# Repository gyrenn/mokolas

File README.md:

# mokolas
mokolo mokolok mokoloja

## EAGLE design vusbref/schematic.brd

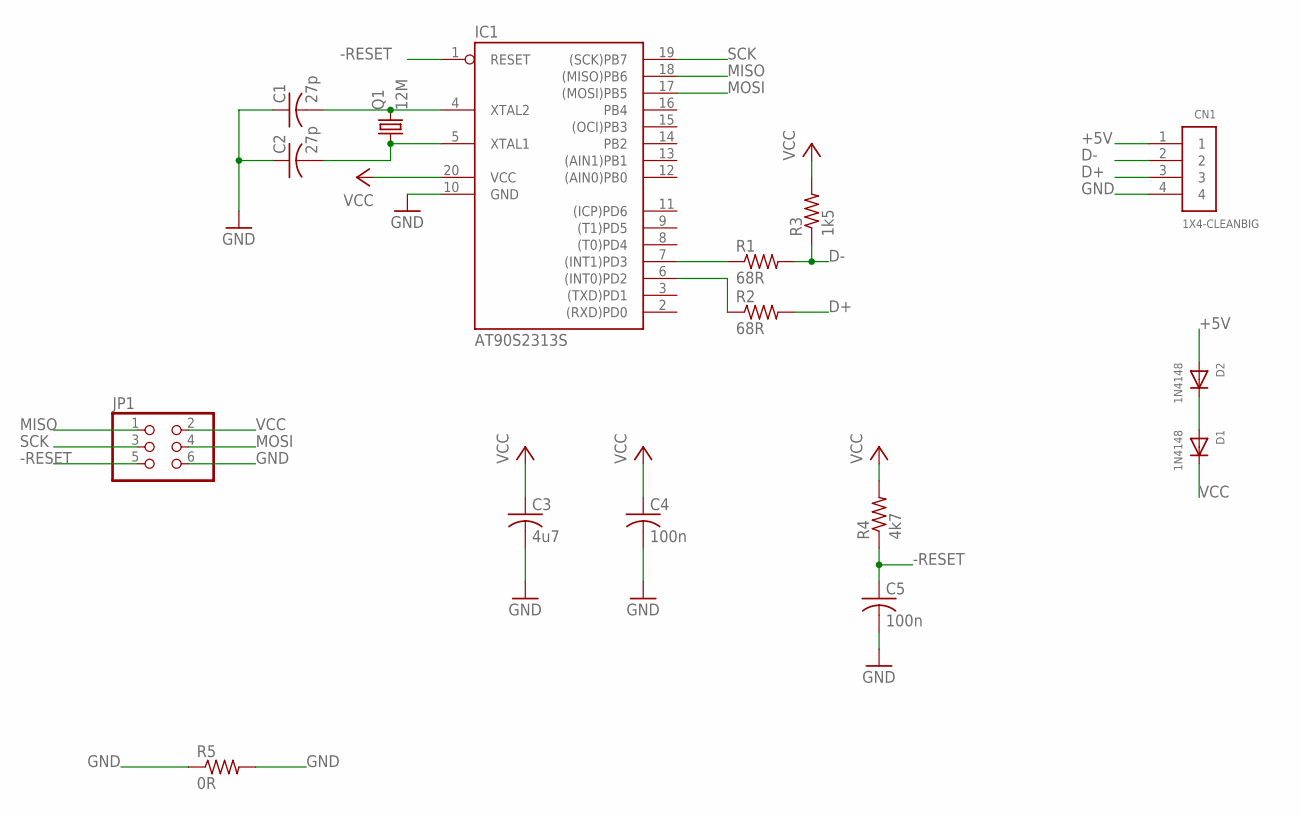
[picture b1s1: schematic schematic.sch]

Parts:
C1, C2: 27p; C0805
C3: 4u7; C0805
C4, C5: 100n; C0805
CN1: 1X4-CLEANBIG; 1X04-CLEANBIG
D1, D2: 1N4148; SMADIODE
IC1: AT90S2313S; SO20L
JP1: PINHD-2X3; 2X03
Q1: 12M; HC49UP
R1, R2: 68R; R0805
R3: 1k5; R0805
R4: 4k7; R0805
R5: 0R; R1206

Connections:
+5V: CN1.1, D2.A
-RESET: C5.1, IC1.1 (RESET), JP1.5, R4.1
D+: CN1.3, R2.2
D-: CN1.2, R1.2, R3.1
GND: C1.1, C2.1, C3.2, C4.2, C5.2, CN1.4, IC1.10 (GND), JP1.6, R5.1, R5.2
MISO: IC1.18 ((MISO)PB6), JP1.1
MOSI: IC1.17 ((MOSI)PB5), JP1.4
unnamed: C1.2, IC1.4 (XTAL2), Q1.2
unnamed: C2.2, IC1.5 (XTAL1), Q1.1
unnamed: IC1.7 ((INT1)PD3), R1.1
unnamed: D1.A, D2.C
unnamed: IC1.6 ((INT0)PD2), R2.1
SCK: IC1.19 ((SCK)PB7), JP1.3
VCC: C3.1, C4.1, D1.C, IC1.20 (VCC), JP1.2, R3.2, R4.2

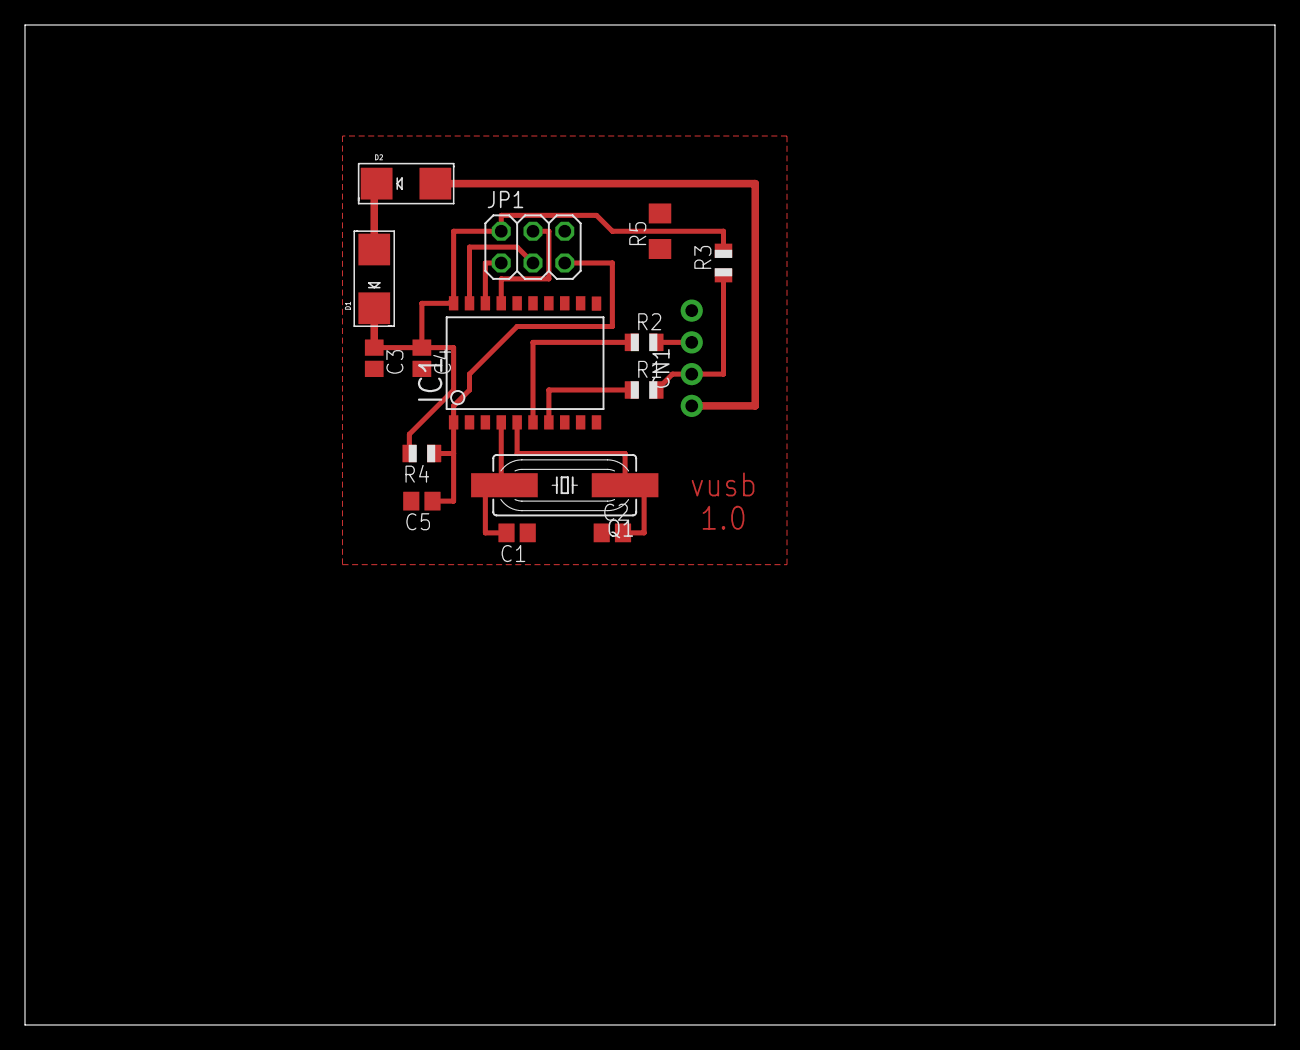
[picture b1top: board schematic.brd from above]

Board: 2 copper layers, 100.0 x 80.0 mm, 16 parts (0 on the bottom side), 14 nets.

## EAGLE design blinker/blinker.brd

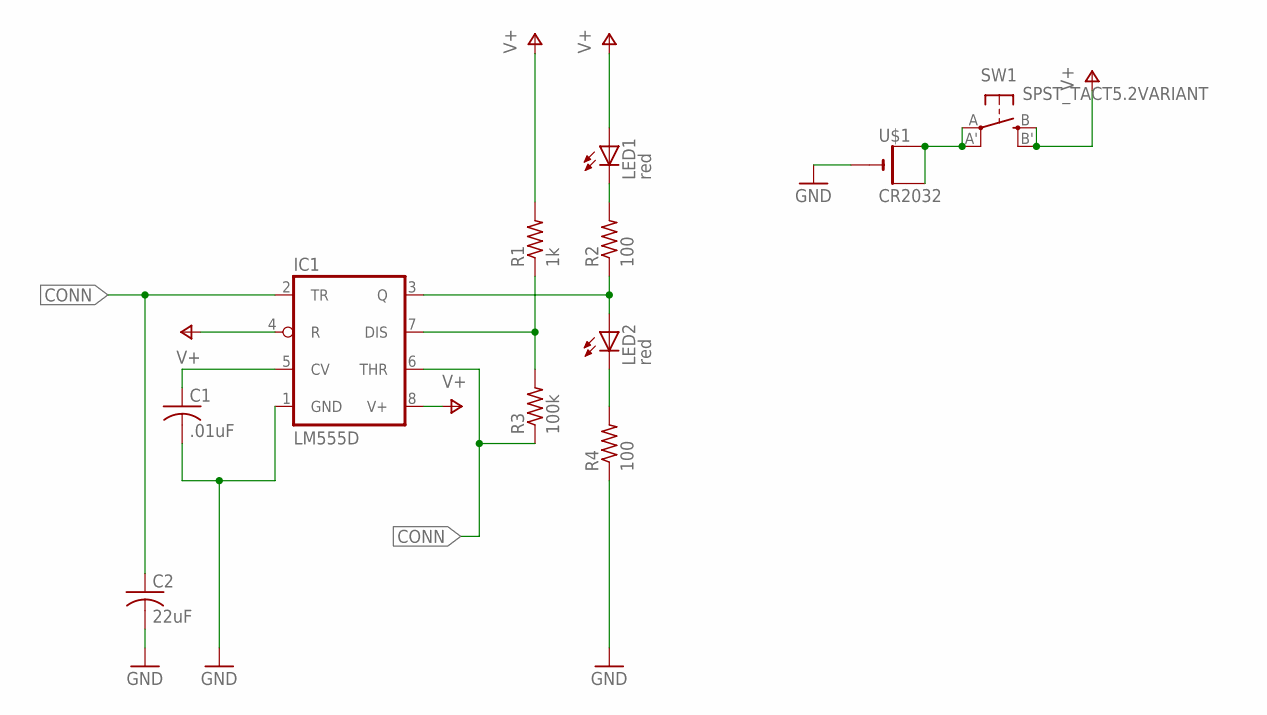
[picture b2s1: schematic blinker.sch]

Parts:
C1: .01uF; C0805
C2: 22uF; C0805
IC1: LM555D; SO08
LED1, LED2: red; CHIPLED_0805
R1: 1k; R0805
R2, R4: 100; R0805
R3: 100k; R0805
SW1: SPST_TACT5.2VARIANT; 5.2X5.2
U$1: CR2032; CR2032-SMD

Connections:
CONN: C2.1, IC1.2 (TR), IC1.6 (THR), R3.1
GND: C1.2, C2.2, IC1.1 (GND), R4.1, U$1.-
unnamed: LED1.C, R2.2
unnamed: IC1.3 (Q), LED2.A, R2.1
unnamed: LED2.C, R4.2
unnamed: IC1.7 (DIS), R1.1, R3.2
unnamed: C1.1, IC1.5 (CV)
unnamed: SW1.A, SW1.A' (P1), U$1.+$1 (+), U$1.+$2 (+1)
V+: IC1.4 (R), IC1.8 (V+), LED1.A, R1.2, SW1.B (S), SW1.B' (S1)

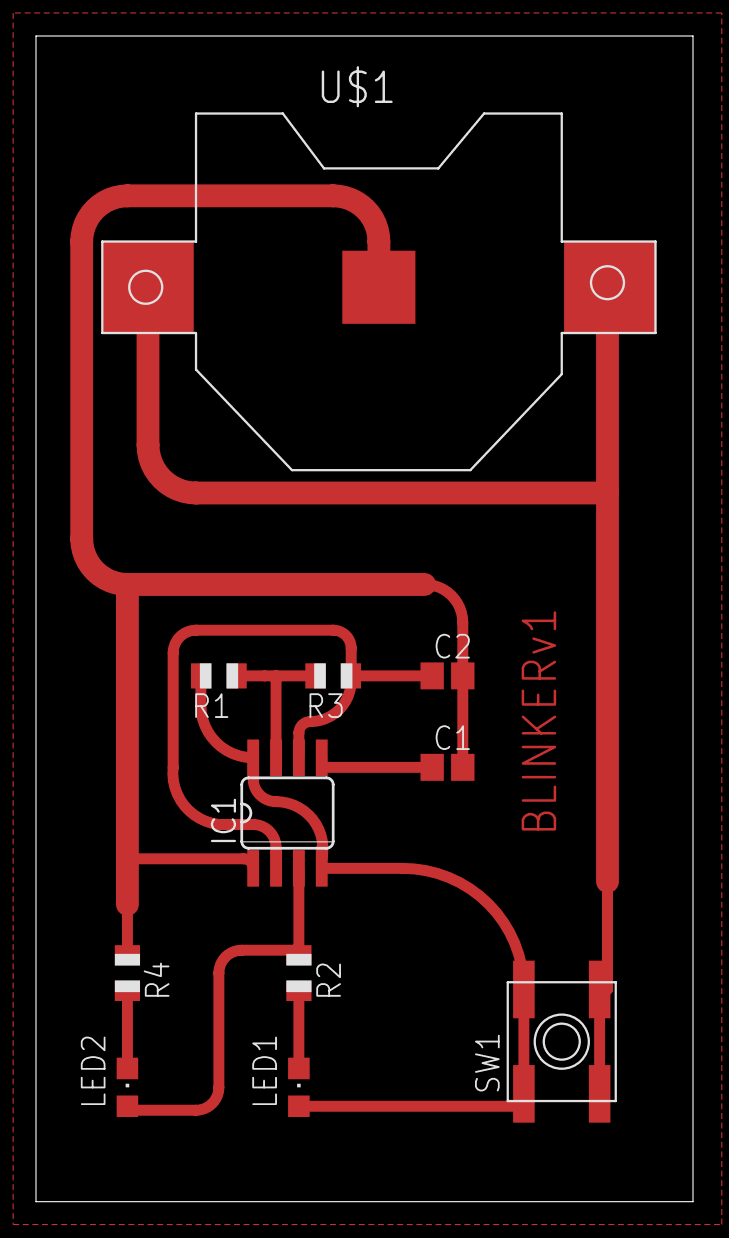
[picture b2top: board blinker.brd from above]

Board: 2 copper layers, 36.5 x 64.8 mm, 11 parts (0 on the bottom side), 9 nets.

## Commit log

2017-01-03 Final
2017-01-03 test file
2017-01-08 new temp sensor & display all sensors
2017-06-28 Add Initial schematic for Alexandra
2017-06-29 Tactile switch drawings, re-organise
2017-07-03 Add application note for ISP
2017-07-03 Added ISP header, resized labels
2017-07-03 Remove backup files
2017-07-03 Add AN for bypass cap design
2017-07-04 Add blinker
2017-07-06 Blinker component size changes
    Also added gitignore, and some datasheets
2017-07-08 Added mokerek's own Eagle library
2017-07-08 Move .gitignore to root
    To avoid temporary eagle files showing up
2017-07-08 PCB design is ready for Blinker
2017-07-09 Added ground plane
2017-07-09 Extended ground plane, added PDF for TT
2017-07-09 Increased Thermal Isolation
2017-07-09 Adjust CR2032 battery holder
    Copied the Battery Holder from Adafruit, and modified it slightly to
    match my version.
2017-07-09 CR2032 Batt holder amended, PCB design update
2017-10-25 Add vusbref project
